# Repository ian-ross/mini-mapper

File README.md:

# Mapping robot project experiment

Goals:

 - Learn some electronics
 - Write some interesting embedded software
 - Experiment with developing teaching materials

## Tools

 - KiCad 5.1.6

## Notes

 - All KiCad projects need to include path to top-level `lib`
   directory as a project-specific library path. This should be set up
   as a path relative to `${KIPRJMOD}`.

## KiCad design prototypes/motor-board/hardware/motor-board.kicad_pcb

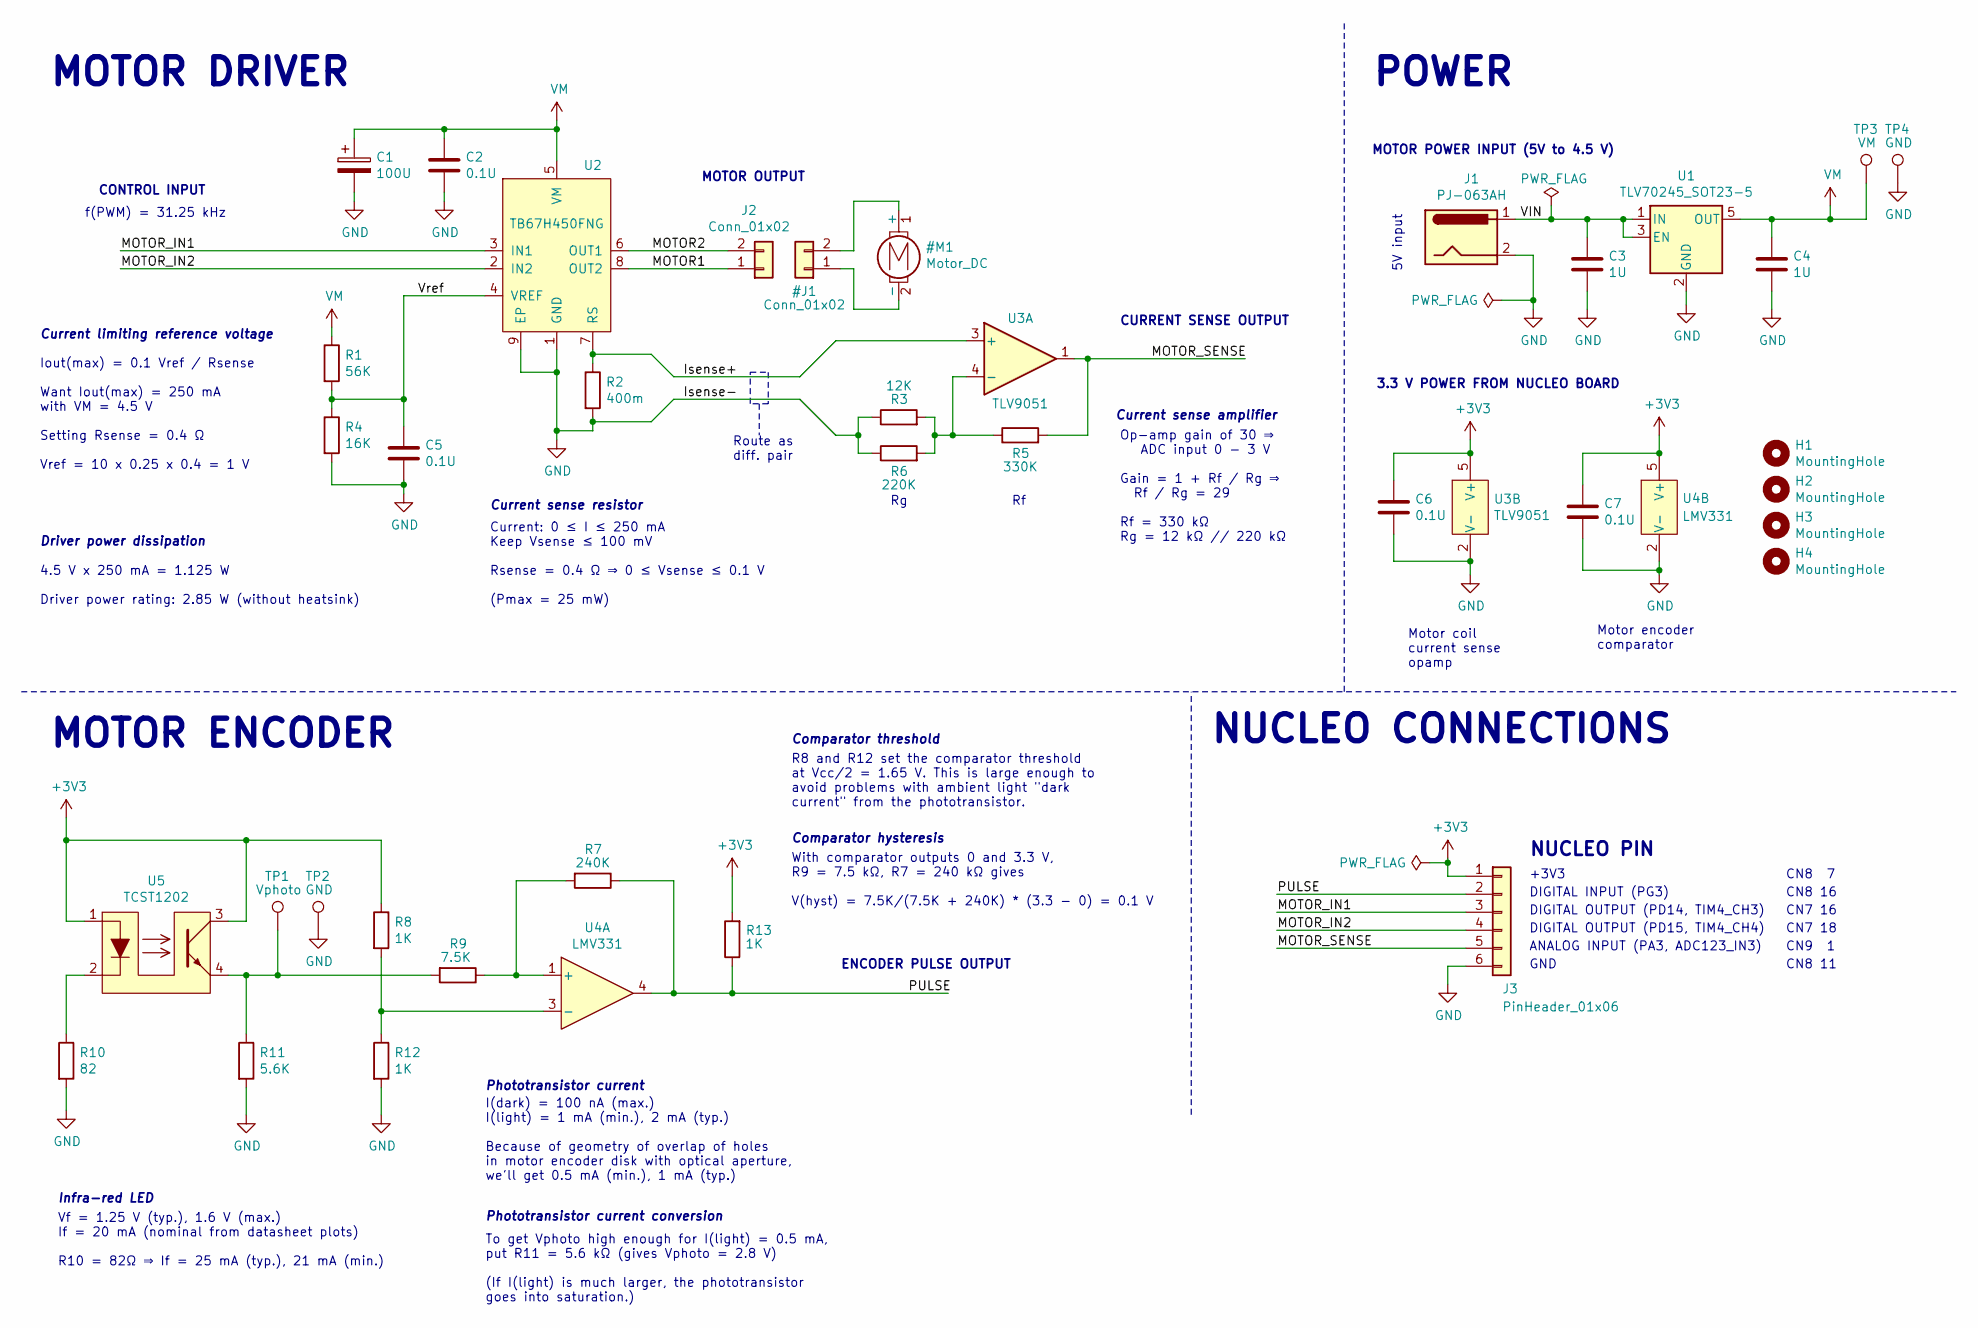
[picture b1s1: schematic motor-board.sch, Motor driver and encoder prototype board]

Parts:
C1: 100U; CP_Elec_6.3x7.7; MPN EEE-HC1C101XP
C2, C5, C6, C7: 0.1U; C_0805; MPN 885012207098
C3, C4: 1U; C_0805; MPN 885012107015
H1, H2, H3, H4: MountingHole; MountingHole_2.7mm_M2.5; MPN n/a
J1: PJ-063AH; BarrelJack_CUI_PJ-063AH_Horizontal; MPN PJ-063AH
J2: Conn_01x02; PinSocket_1x02_P2.54mm_Vertical; MPN SLW-102-01-T-S
J3: PinHeader_01x06; PinHeader_1x06_P2.54mm_Vertical; MPN 22-28-4060
R1: 56K; R_0805; MPN CRGP0805F56K
R2: 400m; R_0805; MPN RL0805FR-070R4L
R3: 12K; R_0805; MPN CRCW080512K0FKEA
R4: 16K; R_0805; MPN CRCW080516K0FKEA
R5: 330K; R_0805; MPN CRCW0805330KFKEA
R6: 220K; R_0805; MPN CRGP0805F220K
R7: 240K; R_0805; MPN CRCW0805240KFKEA
R8, R12: 1K; R_0805; MPN CRGP0805F1K0
R9: 7.5K; R_0805; MPN CRCW08057K50FKEA
R10: 82; R_0805; MPN CRCW080582R0FKEA
R11: 5.6K; R_0805; MPN CRCW08055K60FKEAC
R13: 1K; R_0805; MPN CRCW0805240KFKEA
TP1: Vphoto; TestPoint_Pad_2.0x2.0mm; MPN n/a
TP2, TP4: GND; TestPoint_Pad_2.0x2.0mm; MPN n/a
TP3: VM; TestPoint_Pad_2.0x2.0mm; MPN n/a
U1: TLV70245_SOT23-5; SOT-23-5; MPN TLV70245DBVR
U2: TB67H450FNG; SOIC127P600X175-9N; MPN TB67H450FNG
U3: TLV9051; SOT-23-5; MPN TLV9051IDBVR
U4: LMV331; SOT-23-5; MPN LMV331IDBVR
U5: TCST1202; MPN TCST1202

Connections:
+3V3: C6.1, C7.1, J3.1, R8.1, R13.2, U3.5 (V+), U4.5 (V+), U5.1, U5.3
/Isense+: R2.1, U2.7 (RS), U3.3 (+)
/MOTOR1: J2.1, U2.8 (OUT2)
/MOTOR2: J2.2, U2.6 (OUT1)
/MOTOR_IN1: J3.3, U2.3 (IN1)
/MOTOR_IN2: J3.4, U2.2 (IN2)
/MOTOR_SENSE: J3.5, R5.2, U3.1
/PULSE: J3.2, R7.1, R13.1, U4.4
/VIN: C3.1, J1.1, U1.1 (IN), U1.3 (EN)
/Vref: C5.1, R1.2, R4.1, U2.4 (VREF)
GND: C1.2, C2.2, C3.2, C4.2, C5.2, C6.2, C7.2, J1.2, J3.6, R2.2, R3.1, R4.2, R6.1, R10.2, R11.2, R12.2, TP2.1, TP4.1, U1.2 (GND), U2.1 (GND), U2.9 (EP), U3.2 (V-), U4.2 (V-)
unnamed: R3.2, R5.1, R6.2, U3.4 (-)
unnamed: R7.2, R9.1, U4.1 (+)
unnamed: R10.1, U5.2
unnamed: R9.2, R11.1, TP1.1, U5.4
unnamed: R8.2, R12.1, U4.3 (-)
VM: C1.1, C2.1, C4.1, R1.1, TP3.1, U1.5 (OUT), U2.5 (VM)

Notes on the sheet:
Current sense resistor
Current limiting reference voltage
MOTOR OUTPUT
Op-amp gain of 30 ⇒ ADC input 0 - 3 V Gain = 1 + Rf / Rg ⇒ Rf / Rg = 29 Rf = 330 kΩ Rg = 12 kΩ // 220 kΩ
MOTOR POWER INPUT (5V to 4.5 V)
CONTROL INPUT
CURRENT SENSE OUTPUT
Current: 0 ≤ I ≤ 250 mA Keep Vsense ≤ 100 mV Rsense = 0.4 Ω ⇒ 0 ≤ Vsense ≤ 0.1 V (Pmax = 25 mW)
Iout(max) = 0.1 Vref / Rsense Want Iout(max) = 250 mA with VM = 4.5 V Setting Rsense = 0.4 Ω Vref = 10 x 0.25 x 0.4 = 1 V
Route as diff. pair
Current sense amplifier
MOTOR DRIVER
MOTOR ENCODER
ENCODER PULSE OUTPUT
Vf = 1.25 V (typ.), 1.6 V (max.) If = 20 mA (nominal from datasheet plots) R10 = 82Ω ⇒ If = 25 mA (typ.), 21 mA (min.)
3.3 V POWER FROM NUCLEO BOARD
Motor coil current sense opamp
Motor encoder comparator
I(dark) = 100 nA (max.) I(light) = 1 mA (min.), 2 mA (typ.) Because of geometry of overlap of holes in motor encoder disk with optical aperture, we'll get 0.5 mA (min.), 1 mA (typ.)
Infra-red LED
Phototransistor current
To get Vphoto high enough for I(light) = 0.5 mA, put R11 = 5.6 kΩ (gives Vphoto = 2.8 V) (If I(light) is much larger, the phototransistor goes into saturation.)
Phototransistor current conversion
Comparator hysteresis
With comparator outputs 0 and 3.3 V, R9 = 7.5 kΩ, R7 = 240 kΩ gives V(hyst) = 7.5K/(7.5K + 240K) * (3.3 - 0) = 0.1 V
Comparator threshold
R8 and R12 set the comparator threshold at Vcc/2 = 1.65 V. This is large enough to avoid problems with ambient light "dark current" from the phototransistor.
POWER
5V input
NUCLEO CONNECTIONS
+3V3
GND
DIGITAL OUTPUT (PD14, TIM4_CH3)
DIGITAL OUTPUT (PD15, TIM4_CH4)
ANALOG INPUT (PA3, ADC123_IN3)
DIGITAL INPUT (PG3)
NUCLEO PIN
CN8 7
CN8 11
CN7 16

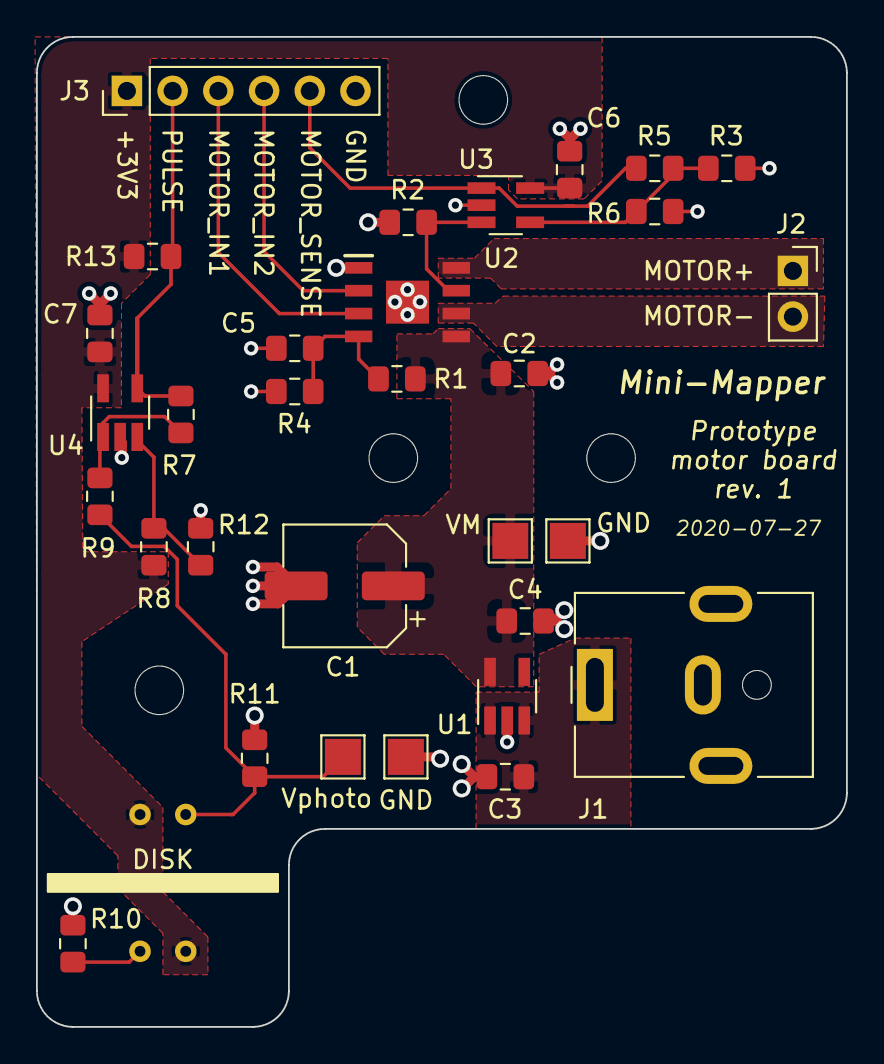
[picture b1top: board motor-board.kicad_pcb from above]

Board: 2 copper layers, 45.0 x 55.0 mm, 36 parts (1 on the bottom side), 17 nets.

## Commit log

2020-06-26 Motor driver comparison; KiCad setup; start motor board schematic
2020-06-27 Added datasheet list
2020-06-27 Tidying
2020-06-28 MCAD for chassis and motor
2020-06-28 Fix corrupted KiCad symbol library metadata
2020-07-01 Correct sense resistor value
2020-07-01 Add some footprints to library symbols
2020-07-03 Add some more footprints; set up link field for symbols
2020-07-05 More mechanical models
2020-07-08 Mechanical modelling for motor encoder setup
2020-07-08 Small improvements to motor prototype schematic
    - Move motor off board
    - Set up to route current sensing connection as differential pair
2020-07-11 Moved some thing around; photointerrupter signal calculation
2020-07-12 More MCAD; photointerrupter comparison spreadsheet
2020-07-15 Photoencoder signal calculations
2020-07-19 More work on motor encoder; KiCad library reorganisation
2020-07-19 Motor encoder comparator setup
2020-07-22 Tidy up motor encoder; simulations; start on power
2020-07-22 More on simulations; motor board power
2020-07-22 Ignores
2020-07-22 Remove ignored files before BFG cleanup
2020-07-23 Motor board schematic close to complete
2020-07-25 Finish up motor board schematic; start on layout
2020-07-27 Finished layout; checklists
2020-07-27 Missed some changes...
2020-07-27 Checklist...
2020-07-28 Finalise motor board layout; schematic and layout checklist
2020-07-28 Updated BOM spreadsheet
2020-07-29 Motor prototype setup CAD model
2020-07-30 Modify motor encoder disk template
2020-07-31 Motor encoder disks: manual attempt, then PCB version
2020-08-04 Starting on code: STM32F767ZI Nucleo BSP and test blinkies
2020-08-05 Add semihosting example
2020-08-08 Rough serial output
2020-08-10 Some reorganisation
2020-08-10 Basic RX handling: interrupt, buffer, line handling
2020-08-11 Reorganise BSP code
2020-08-11 First go at USART transmit DMA
2020-08-12 WIP: build tools; serial terminal using DMA TX
2020-09-08 WIP: start of TDD reorganisation
    - Set up for host build and test
    - Reorganise CMSIS headers for host build
    - Initial tests using doctest and trompeloeil
2020-09-08 Blinky demo with event manager and HAL
2020-09-08 USART TDD
2020-09-09 Add basic SysTick USART demo
2020-09-10 Terminal TDD
2020-09-10 Terminal demo
2020-09-12 Command shell TDD
2020-09-12 Shell-driven blinky; commenting
2020-09-12 Cleanup
2020-09-26 Reorganise hardware initialisation
2020-09-27 Get PWM shell demo working
2020-10-26 Extend PWM code to support multiple channels
2020-10-26 Assembly helper
2020-10-26 Start motor driver TDD
2020-10-26 First round of motor driver TDD
2020-11-26 WIP: Waveforms setup for motor board testing; motor torque code
2020-11-27 Motor torque TDD; hardware mocking improvements
2020-11-27 Motor torque TDD: data collection
2020-11-29 Motor encoder TDD
2020-11-30 Rough speed calculations in motor encoder
2020-11-30 Motor controller TDD
2020-12-02 Motor shell application
2020-12-06 WIP: motor PWM working in shell-motor app
2020-12-06 WIP: motor torque data collection working
2020-12-06 WIP: motor encoder working in shell-motor app
2020-12-13 Waveforms setup
